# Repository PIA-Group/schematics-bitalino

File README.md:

# BITalino Schematics

PCB schematics and physical drawings for the original BITalino (https://www.bitalino.com) biomedical development toolkit, which includes Molex Sherlock connectors footprint and pin
breakout. Source files (.brd & .sch) can be opened with AutoDesk's EAGLE PCB design software: https://www.autodesk.com/products/eagle/overview

## Publications

Diana Baptista, Hugo Plácido da Silva and Ana Fred. [Experimental Characterization and Analysis of the BITalino Platforms Against a Reference Device](https://ieeexplore.ieee.org/abstract/document/8037344/). In *Proc. of the IEEE Engineering in Medicine and Biology Society Annual Int’l Conf. (EMBC)*, pp. 2418-2421, 2017

Hugo Plácido da Silva, Carlos Carreiras, André Lourenço, Ana Fred, Rui César das Neves and Rui Ferreira. [Off-the-person electrocardiography: performance assessment and clinical correlation](https://link.springer.com/article/10.1007%2Fs12553-015-0098-y). *Health and Technology*, 4(4), pp. 309-318, Springer, 2015

Hugo Plácido da Silva, Ana Fred and Raúl Martins. [Biosignals for Everyone](https://ieeexplore.ieee.org/xpl/articleDetails.jsp?arnumber=6926682). *IEEE Pervasive Computing*, 13(4):64-71, 2014

Hugo Plácido da Silva, André Lourenço, Ana Fred and Raúl Martins. [BIT: Biosignal Igniter Toolkit](https://sciencedirect.com/science/article/pii/S0169260714000984). *Computer Methods and Programs in Biomedicine*, 115(1):20-32, 2014

Hugo Plácido da Silva, José Guerreiro, André Lourenço, Ana Fred and Raúl Martins. [BITalino: A novel hardware framework for physiological computing](https://www.researchgate.net/publication/260987402_BITalino_A_Novel_Hardware_Framework_for_Physiological_Computing). In *Proc. of the Int’l Conf. on Physiological Computing Systems (PhyCS)*, pp. 246-253, 2014

José Guerreiro, André Lourenço, Hugo Plácido da Silva and Ana Fred. [Performance comparison of low-cost hardware platforms targeting physiological computing applications](https://it.pt/papconf_abs_p.asp?ID_PaperConference=14722&id=4). In *Proc. of the Conf. on Electronics, Telecommunications and Computers (CETC)*, 2013

José Guerreiro, Raúl Martins, Hugo Plácido da Silva, André Lourenço and Ana Fred. [BITalino: A multimodal platform for physiological computing](https://www.researchgate.net/publication/259177489_BITalino_A_Multimodal_Platform_for_Physiological_Computing). In *Proc. of the Int’l Conf. on Informatics in Control, Automation and Robotics (ICINCO)*, pp. 500-506, 2013

Priscila Alves, Hugo Plácido da Silva, André Lourenço and Ana Fred. [BITalino: A biosignal acquisition system based on the Arduino](https://lx.it.pt/~afred/papers/BITalino.pdf). In *Proc. of the Int'l Conf. on Biomedical Electronics and Devices (BIODEVICES)*, pp. 261-264, 2013

## License

See LICENSE for more details.

## Disclaimer

This work is distributed in the hope it will be useful and provided
to you "as is", but WITHOUT ANY WARRANTY, without even the implied
warranty of MERCHANTABILITY or FITNESS FOR A PARTICULAR PURPOSE. This
work is NOT intended for medical diagnosis. We expressly disclaim any
liability whatsoever for any direct, indirect, consequential, incidental
or special damages, including, without limitation, lost revenues, lost
profits, losses resulting from business interruption or loss of data,
regardless of the form of action or legal theory under which the
liability may be asserted, even if advised of the possibility of such
damages.

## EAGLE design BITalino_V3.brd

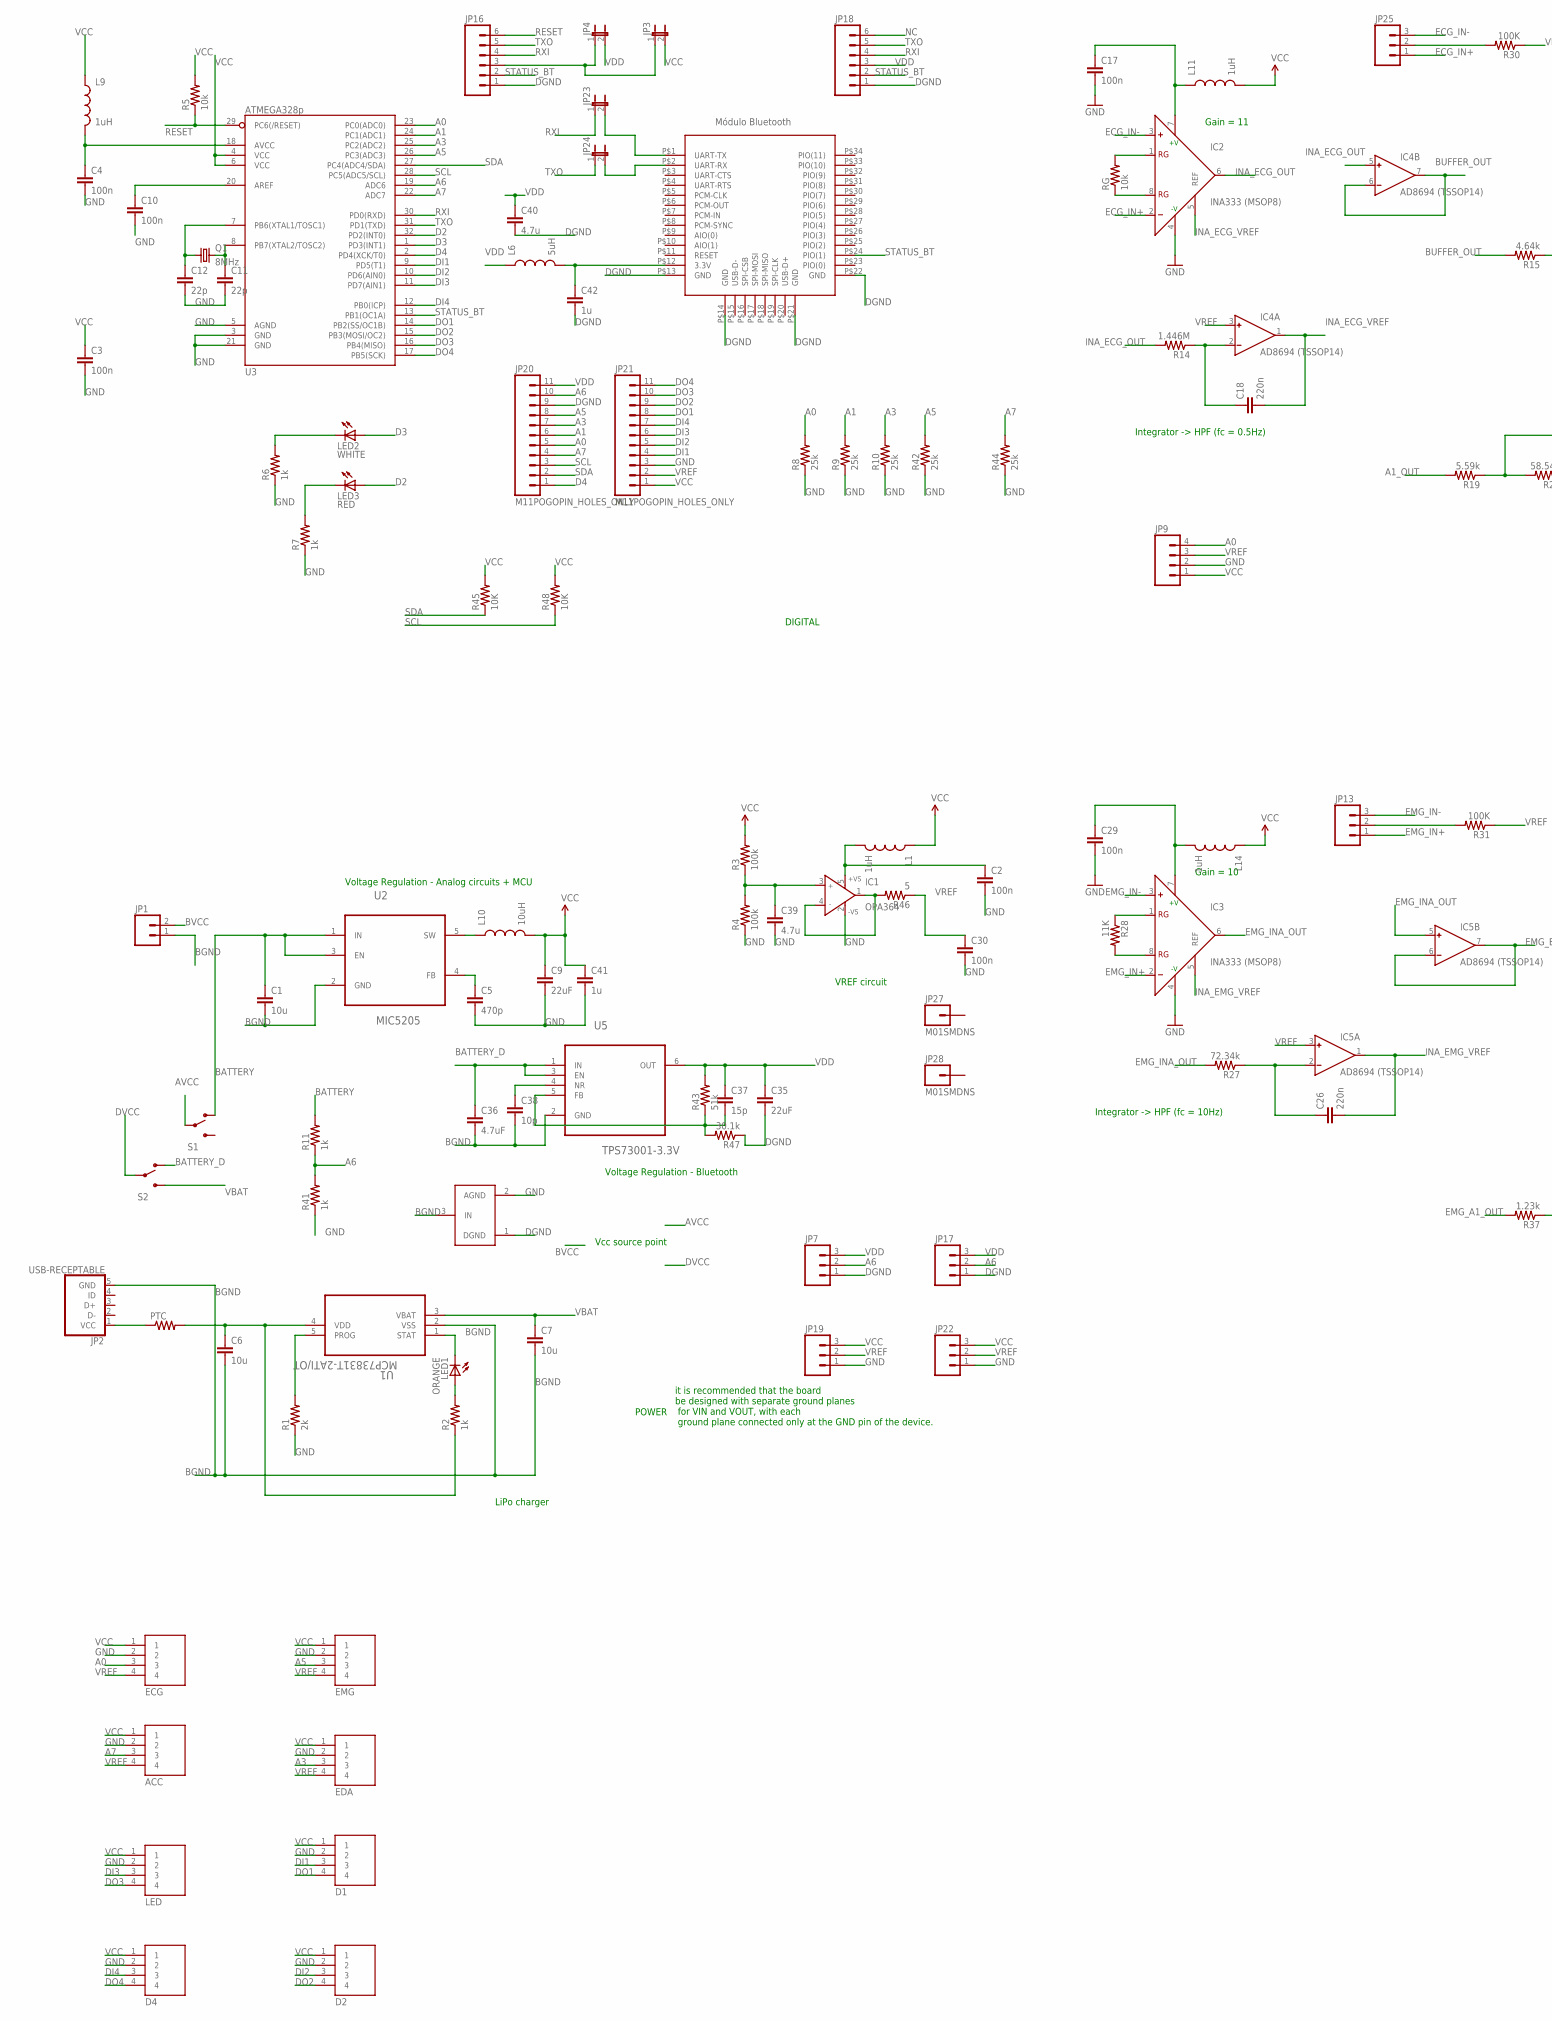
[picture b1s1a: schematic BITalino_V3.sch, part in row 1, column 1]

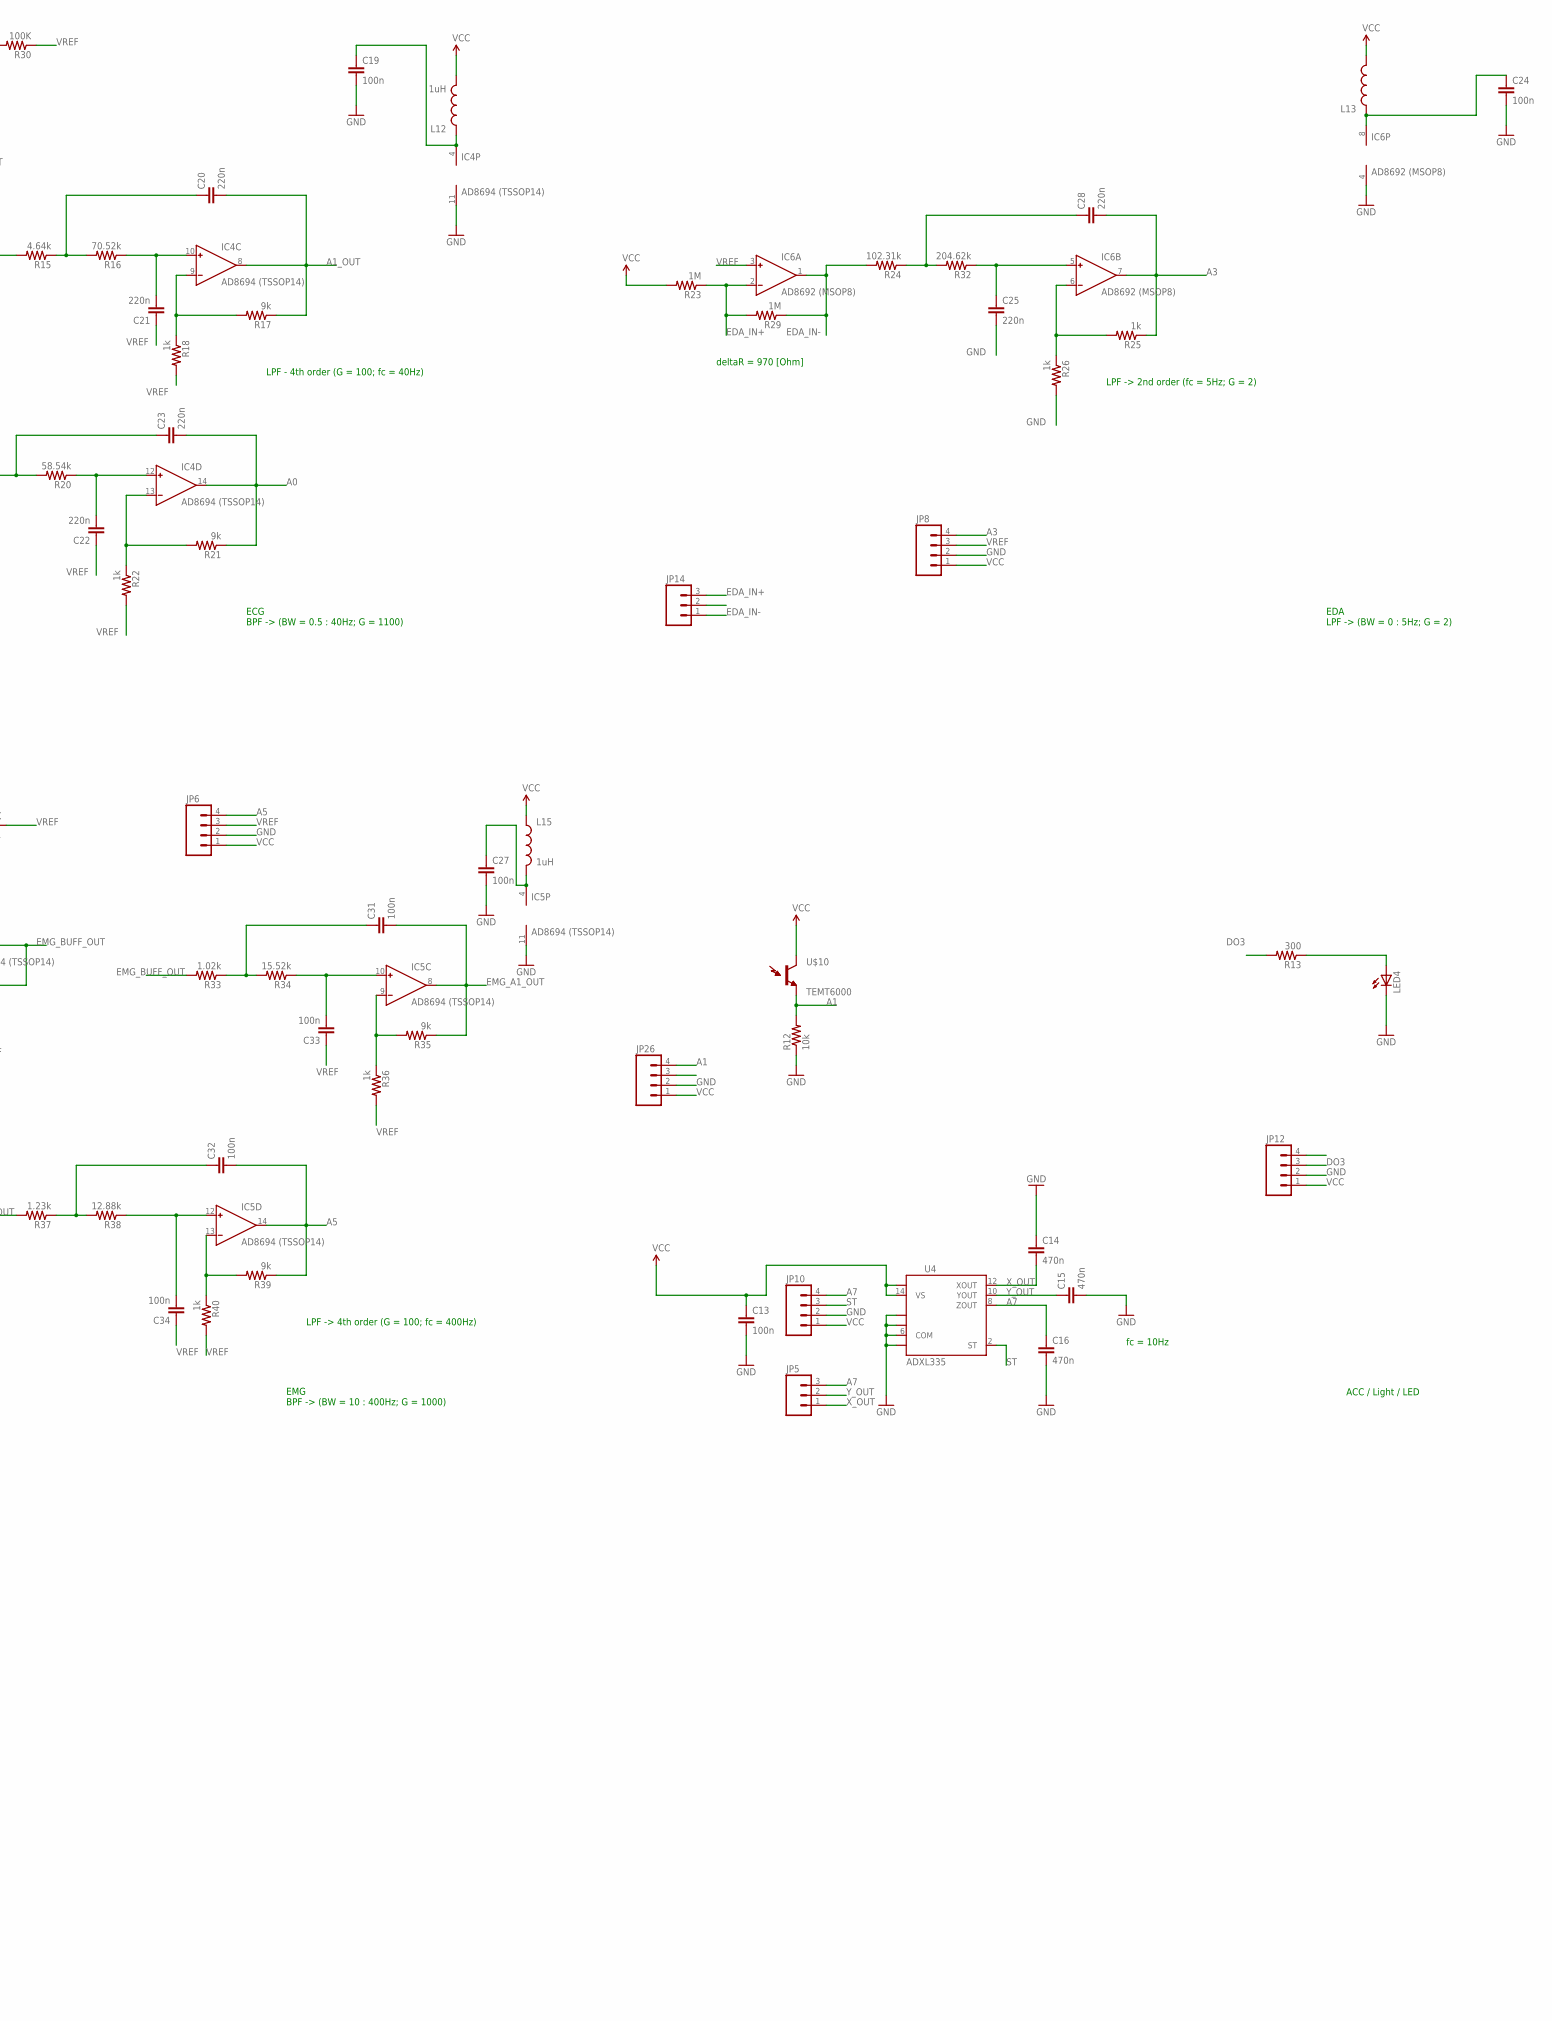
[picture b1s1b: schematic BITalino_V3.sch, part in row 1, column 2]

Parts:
ACC: RJ22; SMD
C1, C6, C7: 10u; 0805
C2, C3, C4, C10, C13, C17, C19, C24, C27, C29, C30, C31, C32, C33, C34: 100n; 0603-CAP
C5: 470p; 0603-CAP
C9, C35: 22uF; 0805
C11, C12: 22p; 0603-CAP
C14, C15, C16: 470n; 0603-CAP
C18, C20, C21, C22, C23, C25, C26, C28: 220n; 0603-CAP
C36: 4.7uF; 0805
C37: 15p; 0603-CAP
C38: 10p; 0603-CAP
C39, C40: 4.7u; 0603-CAP
C41, C42: 1u; 0603-CAP
D1, D2, D4: RJ22; SMD
ECG: RJ22; SMD
EDA: RJ22; SMD
EMG: ECG; SMD
IC1: OPA364; SOT23-5
IC2, IC3: INA333 (MSOP8); MSOP08
IC4, IC5: AD8694 (TSSOP14); TSSOP14
IC6: AD8692 (MSOP8); MSOP08
JP1: M02-JST-2-PTH-NO_SILK; JST-2-PTH-NS
JP2: USB-RECEPTABLE; FCI-10103594-0001LF
JP3, JP4, JP23, JP24: JUMPER-2SMD-NO-NS; SJ_2S-NO-NS
JP5, JP13, JP14, JP25: M03JST-PTH; JST-3-PTH
JP6, JP8, JP9, JP10, JP12, JP26: M04JST-PTH; JST-4-PTH
JP7, JP17, JP19, JP22: M031X03_NO_SILK; 1X03_NO_SILK
JP16, JP18: M06POGOPIN_HOLES_ONLY; 1X06_HOLES_ONLY
JP20, JP21: M11POGOPIN_HOLES_ONLY; 1X11_HOLES_ONLY
JP27, JP28: M01SMDNS; 1X01NS
L1, L9, L11, L12, L14, L15: 1uH; 0603
L6: 5uH; 0805
L10: 10uH; 0805
L13: INDUCTOR0603; 0603
LED: RJ22; SMD
LED1: ORANGE; LED-0603
LED2: WHITE; LED-0603
LED3: RED; LED-0603
LED4: LED1206; LED-1206
PTC: RESISTOR0805-RES; 0805
Q1: 8MHz; CTS406
R1: 2k; 0603-RES
R2, R6, R7, R11, R18, R22, R25, R26, R36, R40, R41: 1k; 0603-RES
R3, R4: 100k; 0603-RES
R5, R12: 10k; 0603-RES
R8, R9, R10, R42, R44: 25k; 0603-RES
R13: 300; 0603-RES
R14: 1.446M; 0603-RES
R15: 4.64k; 0603-RES
R16: 70.52k; 0603-RES
R17, R21, R35, R39: 9k; 0603-RES
R19: 5.59k; 0603-RES
R20: 58.54k; 0603-RES
R23, R29: 1M; 0603-RES
R24: 102.31k; 0603-RES
R27: 72.34k; 0603-RES
R28: 11K; 0603-RES
R30, R31: 100K; 0603-RES
R32: 204.62k; 0603-RES
R33: 1.02k; 0603-RES
R34: 15.52k; 0603-RES
R37: 1.23k; 0603-RES
R38: 12.88k; 0603-RES
R43: 51k; 0603-RES
R45, R48: 10K; 0603-RES
R46: 5; 0603-RES
R47: 30.1k; 0603-RES
RG: 10k; 0603-RES
S1, S2: SWITCH-SPSTPTH; SWITCH-SPDT
U1: MCP73831T-2ATI/OT; SOT95P300X145-5N
U2: MIC5205; SOT95P280X130-5N; MPN ADP2108AUJZ-3.3-R7
U3: ATMEGA328p; TQFP32-08
U4: ADXL335; LFCSP-16
U5: TPS73001-3.3V; SOT95P280X145-6N
U$1: BLUETOOTH
U$2: GND_CONNECT
U$10: TEMT6000; TEMT6000-SEN

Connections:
A0: C23.2, ECG.3, IC4.14 (OUT), JP9.4, JP20.5, R8.2, R21.1, U3.23 (PC0(ADC0))
A1: JP20.6, JP26.4, R9.2, R12.2, U3.24 (PC1(ADC1)), U$10.EMITTER (E1)
A1_OUT: C20.2, IC4.8 (OUT), R17.1, R19.2
A3: C28.2, EDA.3, IC6.7 (OUT), JP8.4, JP20.7, R10.2, R25.1, U3.25 (PC2(ADC2))
A5: C32.2, EMG.3, IC5.14 (OUT), JP6.4, JP20.8, R39.1, R42.2, U3.26 (PC3(ADC3))
A6: JP7.2, JP17.2, JP20.10, R11.1, R41.2, U3.19 (ADC6)
A7: ACC.3, C16.1, JP5.3, JP10.4, JP20.4, R44.2, U3.22 (ADC7), U4.8 (ZOUT)
AVCC: S1.2
BATTERY: C1.1, R11.2, S1.1 (O), U2.1 (IN), U2.3 (EN)
BATTERY_D: C36.1, S2.1 (O), U5.1 (IN), U5.3 (EN)
BGND: C1.2, C6.2, C7.2, C36.2, C38.2, JP1.1, JP2.5 (GND), U1.2 (VSS), U2.2 (GND), U5.2 (GND), U$2.3 (IN)
BUFFER_OUT: IC4.6 (IN-), IC4.7 (OUT), R15.2
BVCC: JP1.2
D2: LED3.A, U3.32 (PD2(INT0))
D3: LED2.A, U3.1 (PD3(INT1))
D4: JP20.1, U3.2 (PD4(XCK/T0))
DGND: C35.2, C40.2, C42.2, JP7.1, JP16.1, JP17.1, JP18.1, JP20.9, R47.1, U$1.P$13 (GND), U$1.P$14 (GND), U$1.P$21 (GND), U$1.P$22 (GND), U$2.1 (DGND)
DI1: D1.3, JP21.4, U3.9 (PD5(T1))
DI2: D2.3, JP21.5, U3.10 (PD6(AIN0))
DI3: JP21.6, LED.3, U3.11 (PD7(AIN1))
DI4: D4.3, JP21.7, U3.12 (PB0(ICP))
DO1: D1.4, JP21.8, U3.14 (PB2(SS/OC1B))
DO2: D2.4, JP21.9, U3.15 (PB3(MOSI/OC2))
DO3: JP12.3, JP21.10, LED.4, R13.2, U3.16 (PB4(MISO))
DO4: D4.4, JP21.11, U3.17 (PB5(SCK))
DVCC: S2.2
ECG_IN+: IC2.2 (-), JP25.1
ECG_IN-: IC2.3 (+), JP25.3
EDA_IN+: IC6.2 (IN-), JP14.3, R23.1, R29.2
EDA_IN-: IC6.1 (OUT), JP14.1, R24.2, R29.1
EMG_A1_OUT: C31.2, IC5.8 (OUT), R35.1, R37.2
EMG_BUFF_OUT: IC5.6 (IN-), IC5.7 (OUT), R33.2
EMG_IN+: IC3.2 (-), JP13.1
EMG_IN-: IC3.3 (+), JP13.3
EMG_INA_OUT: IC3.6 (OUT), IC5.5 (IN+), R27.2
GND: ACC.2, C2.2, C3.2, C4.2, C5.2, C9.2, C10.2, C11.2, C12.2, C13.2, C14.1, C15.2, C16.2, C17.2, C19.2, C24.2, C25.2, C27.2, C29.2, C30.2, C39.2, C41.2, D1.2, D2.2, D4.2, ECG.2, EDA.2, EMG.2, IC1.2 (-VS), IC2.4 (-V), IC3.4 (-V), IC4.11 (V-), IC5.11 (V-), IC6.4 (V-), JP6.2, JP8.2, JP9.2, JP10.2, JP12.2, JP19.1, JP21.3, JP22.1, JP26.2, LED.2, LED4.C, R1.1, R4.1, R6.1, R7.1, R8.1, R9.1, R10.1, R12.1, R26.2, R41.1, R42.1, R44.1, U3.3 (GND), U3.5 (AGND), U3.21 (GND), U4.3 (COM), U4.5 (COM), U4.6 (COM), U4.7 (COM), U$2.2 (AGND)
INA_ECG_OUT: IC2.6 (OUT), IC4.5 (IN+), R14.2
INA_ECG_VREF: C18.2, IC2.5 (REF), IC4.1 (OUT)
INA_EMG_VREF: C26.2, IC3.5 (REF), IC5.1 (OUT)
unnamed: C6.1, PTC.2, R2.1, U1.4 (VDD)
unnamed: R1.2, U1.5 (PROG)
unnamed: LED1.A, R2.2
unnamed: LED1.C, U1.1 (STAT)
unnamed: L10.1, U2.5 (SW)
unnamed: C39.1, IC1.3 (IN+), R3.1, R4.2
unnamed: C38.1, U5.4 (NR)
unnamed: C10.1, U3.20 (AREF)
unnamed: C12.1, Q1.1, U3.7 (PB6(XTAL1/TOSC1))
unnamed: C11.1, Q1.3 (2), U3.8 (PB7(XTAL2/TOSC2))
unnamed: LED2.C, R6.2
unnamed: JP23.2, U$1.P$1 (UART-TX)
unnamed: JP24.2, U$1.P$2 (UART-RX)
unnamed: LED3.C, R7.2
unnamed: C4.1, L9.2, U3.18 (AVCC)
unnamed: C5.1, U2.4 (FB)
unnamed: IC3.1 (RG), R28.1
unnamed: IC3.8 (RG), R28.2
unnamed: JP3.1, JP4.1, JP16.3
unnamed: C29.1, IC3.7 (+V), L14.2
unnamed: C17.1, IC2.7 (+V), L11.1
unnamed: C27.1, IC5.4 (V+), L15.2
unnamed: JP2.1 (VCC), PTC.1
unnamed: LED4.A, R13.1
unnamed: IC2.1 (RG), RG.2
unnamed: IC2.8 (RG), RG.1
unnamed: C18.1, IC4.2 (IN-), R14.1
unnamed: C21.2, IC4.10 (IN+), R16.1
unnamed: C20.1, R15.1, R16.2
unnamed: IC4.9 (IN-), R17.2, R18.1
unnamed: C37.2, R43.1, R47.2, U5.5 (FB)
unnamed: C19.1, IC4.4 (V+), L12.1
unnamed: C28.1, R24.1, R32.2
unnamed: C22.2, IC4.12 (IN+), R20.1
unnamed: C23.1, R19.1, R20.2
unnamed: C25.1, IC6.5 (IN+), R32.1
unnamed: IC4.13 (IN-), R21.2, R22.1
unnamed: IC6.6 (IN-), R25.2, R26.1
unnamed: JP25.2, R30.2
unnamed: C2.1, IC1.5 (+VS), L1.2
unnamed: JP13.2, R31.2
unnamed: C24.1, IC6.8 (V+), L13.1
unnamed: C42.1, L6.2, U$1.P$12 (3.3V)
unnamed: IC1.1 (OUT), IC1.4 (IN-), R46.2
unnamed: C26.1, IC5.2 (IN-), R27.1
unnamed: C33.2, IC5.10 (IN+), R34.1
unnamed: C31.1, R33.1, R34.2
unnamed: IC5.9 (IN-), R35.2, R36.1
unnamed: C34.2, IC5.12 (IN+), R38.1
unnamed: C32.1, R37.1, R38.2
unnamed: IC5.13 (IN-), R39.2, R40.1
NC: JP18.6
RESET: JP16.6, R5.1, U3.29 (PC6(/RESET))
RXI: JP16.4, JP18.4, JP23.1, U3.30 (PD0(RXD))
SCL: JP20.3, R48.1, U3.28 (PC5(ADC5/SCL))
SDA: JP20.2, R45.1, U3.27 (PC4(ADC4/SDA))
ST: JP10.3, U4.2 (ST)
STATUS_BT: JP16.2, JP18.2, U3.13 (PB1(OC1A)), U$1.P$24 (PIO(1))
TXO: JP16.5, JP18.5, JP24.1, U3.31 (PD1(TXD))
VBAT: C7.1, S2.3 (S), U1.3 (VBAT)
VCC: ACC.1, C3.1, C9.1, C13.1, C41.1, D1.1, D2.1, D4.1, ECG.1, EDA.1, EMG.1, JP3.2, JP6.1, JP8.1, JP9.1, JP10.1, JP12.1, JP19.3, JP21.1, JP22.3, JP26.1, L1.1, L9.1, L10.2, L11.2, L12.2, L13.2, L14.1, L15.1, LED.1, R3.2, R5.2, R23.2, R45.2, R48.2, U3.4 (VCC), U3.6 (VCC), U4.14 (VS), U4.15 (VS), U$10.COLLECTOR (C1)
VDD: C35.1, C37.1, C40.1, JP4.2, JP7.3, JP17.3, JP18.3, JP20.11, L6.1, R43.2, U5.6 (OUT)
VREF: ACC.4, C21.1, C22.1, C30.1, C33.1, C34.1, ECG.4, EDA.4, EMG.4, IC4.3 (IN+), IC5.3 (IN+), IC6.3 (IN+), JP6.3, JP8.3, JP9.3, JP19.2, JP21.2, JP22.2, R18.2, R22.2, R30.1, R31.1, R36.2, R40.2, R46.1
X_OUT: C14.2, JP5.1, U4.12 (XOUT)
Y_OUT: C15.1, JP5.2, U4.10 (YOUT)

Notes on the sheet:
DIGITAL
POWER
Gain = 11
LPF - 4th order (G = 100; fc = 40Hz)
Integrator -> HPF (fc = 0.5Hz)
deltaR = 970 [Ohm]
LPF -> 2nd order (fc = 5Hz; G = 2)
Gain = 10
Integrator -> HPF (fc = 10Hz)
LPF -> 4th order (G = 100; fc = 400Hz)
EMG BPF -> (BW = 10 : 400Hz; G = 1000)
ECG BPF -> (BW = 0.5 : 40Hz; G = 1100)
EDA LPF -> (BW = 0 : 5Hz; G = 2)
ACC / Light / LED
LiPo charger
Voltage Regulation - Analog circuits + MCU
VREF circuit
Voltage Regulation - Bluetooth
fc = 10Hz
it is recommended that the board be designed with separate ground planes for VIN and VOUT, with each ground plane connected only at the GND pin of the device.
Vcc source point

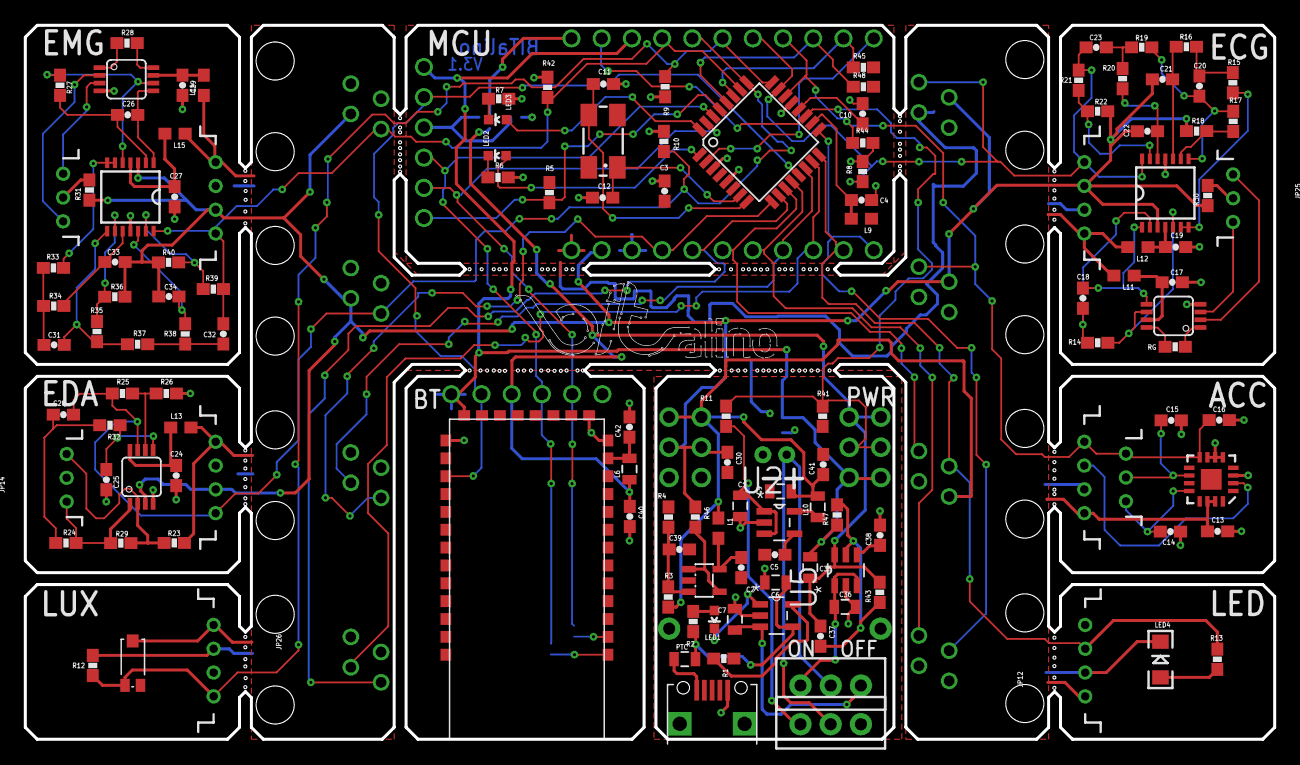
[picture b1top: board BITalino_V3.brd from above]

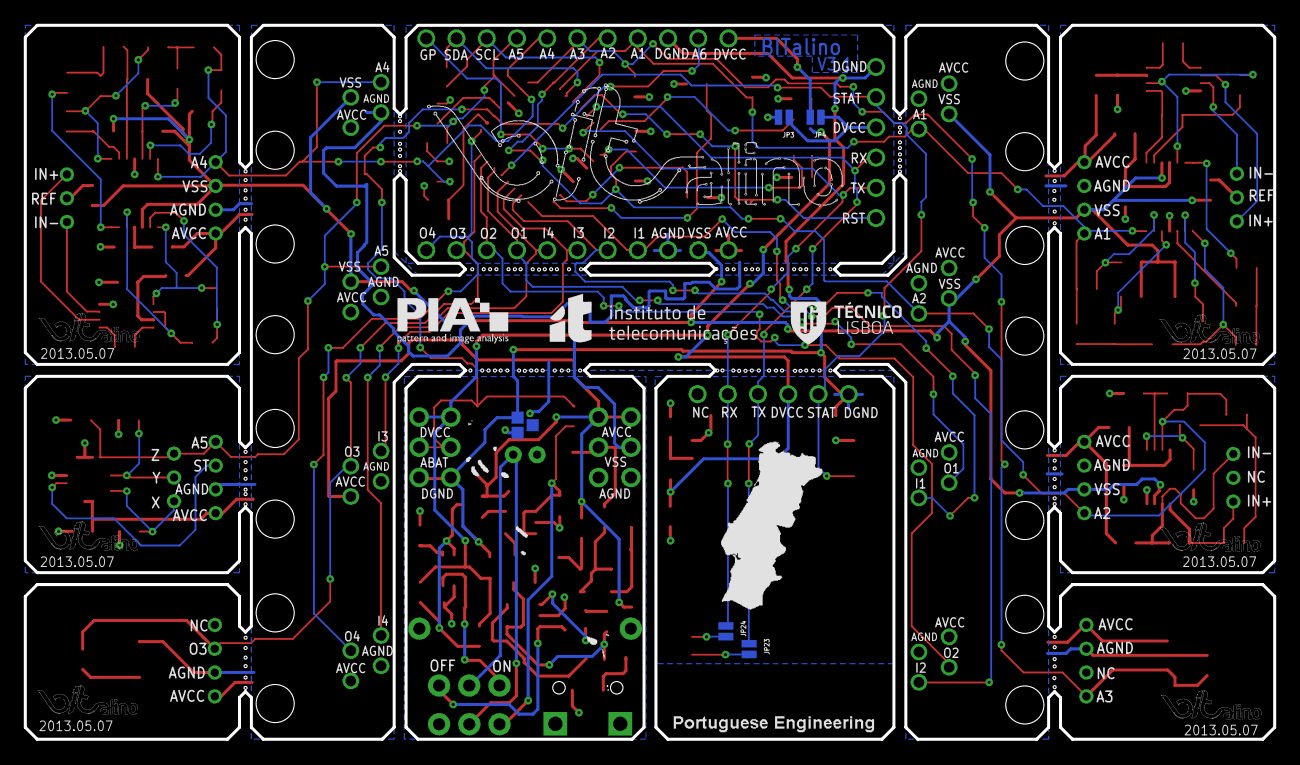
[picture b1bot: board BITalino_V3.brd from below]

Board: 2 copper layers, 105.0 x 60.0 mm, 167 parts (24 on the bottom side), 100 nets.

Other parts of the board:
U$4: BITALINO_LOGO2
U$5: IT_LOGO
U$6: TECNICO_LOGO
U$7: PIA_LOGO
U$8: BITALINO_LOGO2_SMALL
U$9: PT_IMAGE
U$11, U$12, U$13, U$14, U$15, U$16: BITALINO_LOGO2_SENSORS

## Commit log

2019-03-26 Added schematics, board and project
2019-03-26 Rename LICENSE.md to LICENSE
2019-03-26 Update LICENSE

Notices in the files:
parts and their libraries:
SparkFun: Licensing: CC v3.0 Share-Alike You are welcome to use this library for commercial purposes.
